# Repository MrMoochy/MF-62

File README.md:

All files are in master branch
Todos los archivos estan en la rama master

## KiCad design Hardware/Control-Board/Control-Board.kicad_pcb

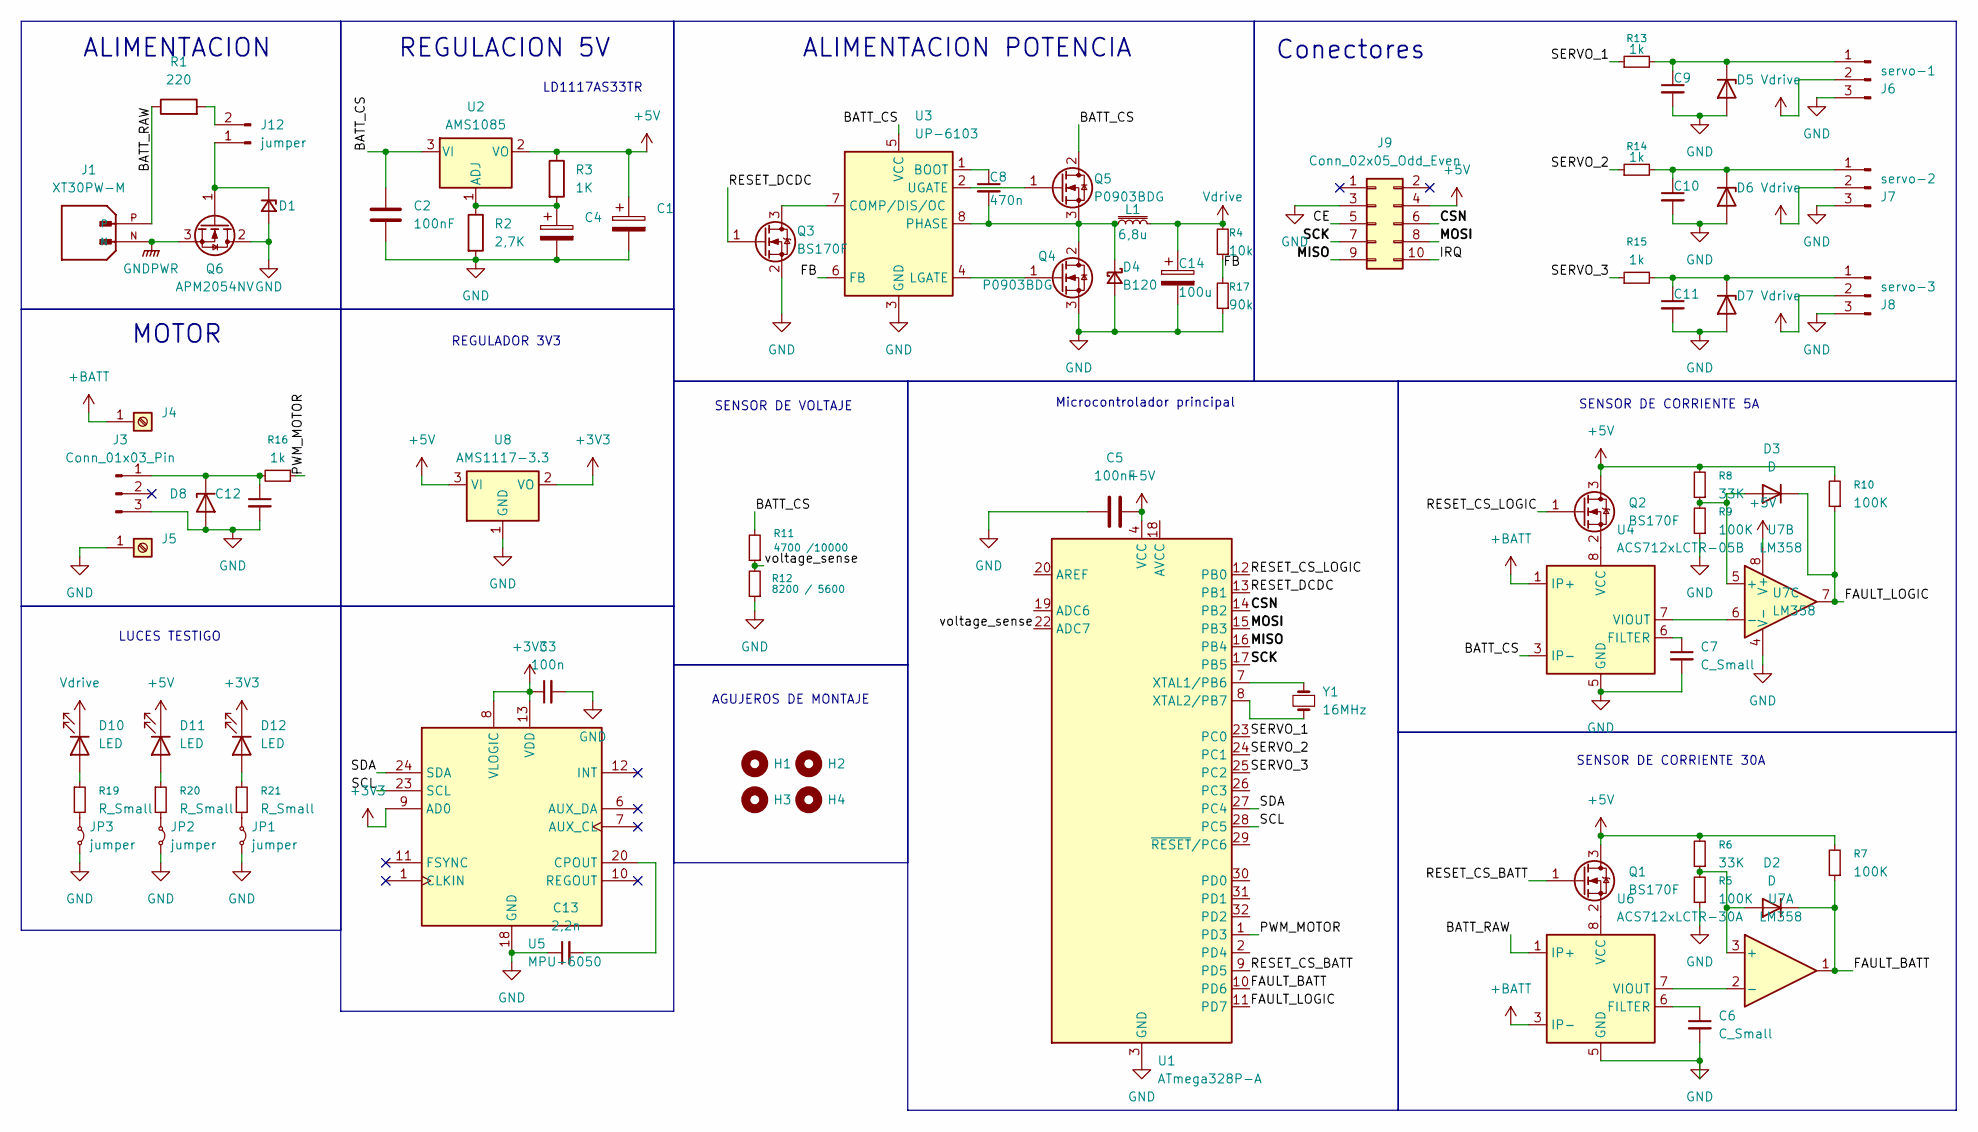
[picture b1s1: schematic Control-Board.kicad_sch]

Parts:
C1: 220uF / 10V; CP_Elec_6.3x4.5
C2: 100nF; C_0805_2012Metric_Pad1.18x1.45mm_HandSolder
C3: 100n; C_0805_2012Metric_Pad1.18x1.45mm_HandSolder
C4: <10uF / 10V; CP_Elec_5x4.4
C5: 100nF; C_0402_1005Metric_Pad0.74x0.62mm_HandSolder
C6, C7, C9, C10, C11, C12: C_Small; C_0805_2012Metric_Pad1.18x1.45mm_HandSolder
C8: 470n; C_0805_2012Metric_Pad1.18x1.45mm_HandSolder
C13: 2,2n; C_0805_2012Metric_Pad1.18x1.45mm_HandSolder
C14: 100u; CP_Elec_5x5.7
D1: mmsz5246bt1g; D_SOD-123
D2, D3: D; D_SOD-123
D4: B120; D_SMA
D5, D6, D7, D8: ESD5Zxx; D_SOD-523
D10, D11, D12: LED; LED_0805_2012Metric_Pad1.15x1.40mm_HandSolder
H1, H2, H3, H4: Mounting_Hole; MountingHole_2.2mm_M2_ISO7380
J1: XT30PW-M; AMASS_XT30PW-M; PARTREV 1.2
J3: Conn_01x03_Pin; PinHeader_1x03_P2.54mm_Horizontal
J4, J5: Screw_Terminal_01x01; Cable_Doble_1,5mm
J6: servo-1; PinHeader_1x03_P2.54mm_Horizontal
J7: servo-2; PinHeader_1x03_P2.54mm_Horizontal
J8: servo-3; PinHeader_1x03_P2.54mm_Horizontal
J9: Conn_02x05_Odd_Even; IDC-Header_2x05_P2.54mm_Horizontal
J12: jumper; PinHeader_1x02_P2.54mm_Vertical
JP1, JP2, JP3: jumper; R_0805_2012Metric_Pad1.20x1.40mm_HandSolder
L1: 6,8u; L_6.3x6.3_H3
Q1, Q2, Q3: BS170F; SOT-23
Q4, Q5: P0903BDG; TO-252-2
Q6: APM2054NV; TO-252-2
R1: 220; R_0805_2012Metric_Pad1.20x1.40mm_HandSolder
R2: 2,7K; R_0805_2012Metric_Pad1.20x1.40mm_HandSolder
R3: 1K; R_0805_2012Metric_Pad1.20x1.40mm_HandSolder
R4: 10k; R_0805_2012Metric_Pad1.20x1.40mm_HandSolder
R5, R7, R9, R10: 100K; R_0805_2012Metric_Pad1.20x1.40mm_HandSolder
R6, R8: 33K; R_0805_2012Metric_Pad1.20x1.40mm_HandSolder
R11: 4700 /10000; R_0805_2012Metric_Pad1.20x1.40mm_HandSolder
R12: 8200 / 5600; R_0805_2012Metric_Pad1.20x1.40mm_HandSolder
R13, R14, R15, R16: 1k; R_0805_2012Metric_Pad1.20x1.40mm_HandSolder
R17: 90k; R_0805_2012Metric_Pad1.20x1.40mm_HandSolder
R19, R20, R21: R_Small; R_0805_2012Metric_Pad1.20x1.40mm_HandSolder
U1: ATmega328P-A; TQFP-32_7x7mm_P0.8mm
U2: AMS1085; TO-252-2
U3: UP-6103; SOIC-8_3.9x4.9mm_P1.27mm
U4: ACS712xLCTR-05B; SOIC-8_3.9x4.9mm_P1.27mm
U5: MPU-6050; InvenSense_QFN-24_4x4mm_P0.5mm
U6: ACS712xLCTR-30A; SOIC-8_3.9x4.9mm_P1.27mm
U7: LM358; SOIC-8_3.9x4.9mm_P1.27mm
U8: AMS1117-3.3; SOT-223-3_TabPin2
Y1: 16MHz; Crystal_SMD_3215-2Pin_3.2x1.5mm

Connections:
+3V3: C3.1, D12.1 (K), U5.8 (VLOGIC), U5.9 (AD0), U5.13 (VDD), U8.2 (VO)
+5V: C1.1, C5.2, D11.1 (K), J9.4, Q1.3 (D), Q2.3 (D), R3.1, R6.2, R7.2, R8.2, R10.2, U1.4 (VCC), U1.6 (VCC), U2.2 (VO), U7.8 (V+), U8.3 (VI)
+BATT: J4.1, U4.1 (IP+), U4.2 (IP+), U6.3 (IP-), U6.4 (IP-)
/BATT_CS: C2.1, Q5.2 (D), R11.2, U2.3 (VI), U3.5 (VCC), U4.3 (IP-), U4.4 (IP-)
/BATT_RAW: J1.P, R1.1, U6.1 (IP+), U6.2 (IP+)
/CE: J9.5
/CSN: J9.6, U1.14 (PB2)
/FAULT_BATT: D2.1 (K), R7.1, U1.10 (PD6), U7.1
/FAULT_LOGIC: D3.1 (K), R10.1, U1.11 (PD7), U7.7
/FB: R4.1, R17.2, U3.6 (FB)
/IRQ: J9.10
/MISO: J9.9, U1.16 (PB4)
/MOSI: J9.8, U1.15 (PB3)
/PWM_MOTOR: R16.1, U1.1 (PD3)
/RESET_CS_BATT: Q1.1 (G), U1.9 (PD5)
/RESET_CS_LOGIC: Q2.1 (G), U1.12 (PB0)
/RESET_DCDC: Q3.1 (G), U1.13 (PB1)
/SCK: J9.7, U1.17 (PB5)
/SCL: U1.28 (PC5), U5.23 (SCL)
/SDA: U1.27 (PC4), U5.24 (SDA)
/SERVO_1: R13.1, U1.23 (PC0)
/SERVO_2: R14.1, U1.24 (PC1)
/SERVO_3: R15.1, U1.25 (PC2)
/voltage_sense: R11.1, R12.2, U1.22 (ADC7)
GND: C1.2, C2.2, C3.2, C4.2, C5.1, C6.2, C7.2, C9.2, C10.2, C11.2, C12.2, C13.1, C14.2, D1.2 (A), D4.2 (A), D5.2 (A), D6.2 (A), D7.2 (A), D8.2 (A), J3.3, J5.1, J6.3, J7.3, J8.3, J9.3, JP1.2 (B), JP2.2 (B), JP3.2 (B), Q3.2 (S), Q4.3 (S), Q6.2 (D), R2.2, R5.1, R9.1, R12.1, R17.1, U1.3 (GND), U1.5 (GND), U1.21 (GND), U3.3 (GND), U4.5 (GND), U5.18 (GND), U6.5 (GND), U7.4 (V-), U8.1 (GND)
GNDPWR: J1.N, Q6.3 (S)
unnamed: D1.1 (K), J12.1, Q6.1 (G)
unnamed: D2.2 (A), R5.2, R6.1, U7.3 (+)
unnamed: D3.2 (A), R8.1, R9.2, U7.5 (+)
unnamed: C8.2, D4.1 (K), L1.1, Q4.2 (D), Q5.3 (S), U3.8 (PHASE)
unnamed: C9.1, D5.1 (K), J6.1, R13.2
unnamed: C10.1, D6.1 (K), J7.1, R14.2
unnamed: C11.1, D7.1 (K), J8.1, R15.2
unnamed: C12.1, D8.1 (K), J3.1, R16.2
unnamed: D10.2 (A), R19.1
unnamed: D11.2 (A), R20.1
unnamed: D12.2 (A), R21.1
unnamed: J12.2, R1.2
unnamed: JP1.1 (A), R21.2
unnamed: JP2.1 (A), R20.2
unnamed: JP3.1 (A), R19.2
unnamed: Q1.2 (S), U6.8 (VCC)
unnamed: Q2.2 (S), U4.8 (VCC)
unnamed: Q3.3 (D), U3.7 (COMP/DIS/OC)
unnamed: Q4.1 (G), U3.4 (LGATE)
unnamed: Q5.1 (G), U3.2 (UGATE)
unnamed: U1.7 (XTAL1/PB6), Y1.2
unnamed: U1.8 (XTAL2/PB7), Y1.1
unnamed: C4.1, R2.1, R3.2, U2.1 (ADJ)
unnamed: C8.1, U3.1 (BOOT)
unnamed: C7.1, U4.6 (FILTER)
unnamed: U4.7 (VIOUT), U7.6 (-)
unnamed: C13.2, U5.20 (CPOUT)
unnamed: C6.1, U6.6 (FILTER)
unnamed: U6.7 (VIOUT), U7.2 (-)
Vdrive: C14.1, D10.1 (K), J6.2, J7.2, J8.2, L1.2, R4.2

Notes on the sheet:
ALIMENTACION
Microcontrolador principal
SENSOR DE VOLTAJE
REGULADOR 3V3
REGULACION 5V
ALIMENTACION POTENCIA
SENSOR DE CORRIENTE 5A
LD1117AS33TR
SENSOR DE CORRIENTE 30A
Conectores
LUCES TESTIGO
MOTOR
AGUJEROS DE MONTAJE

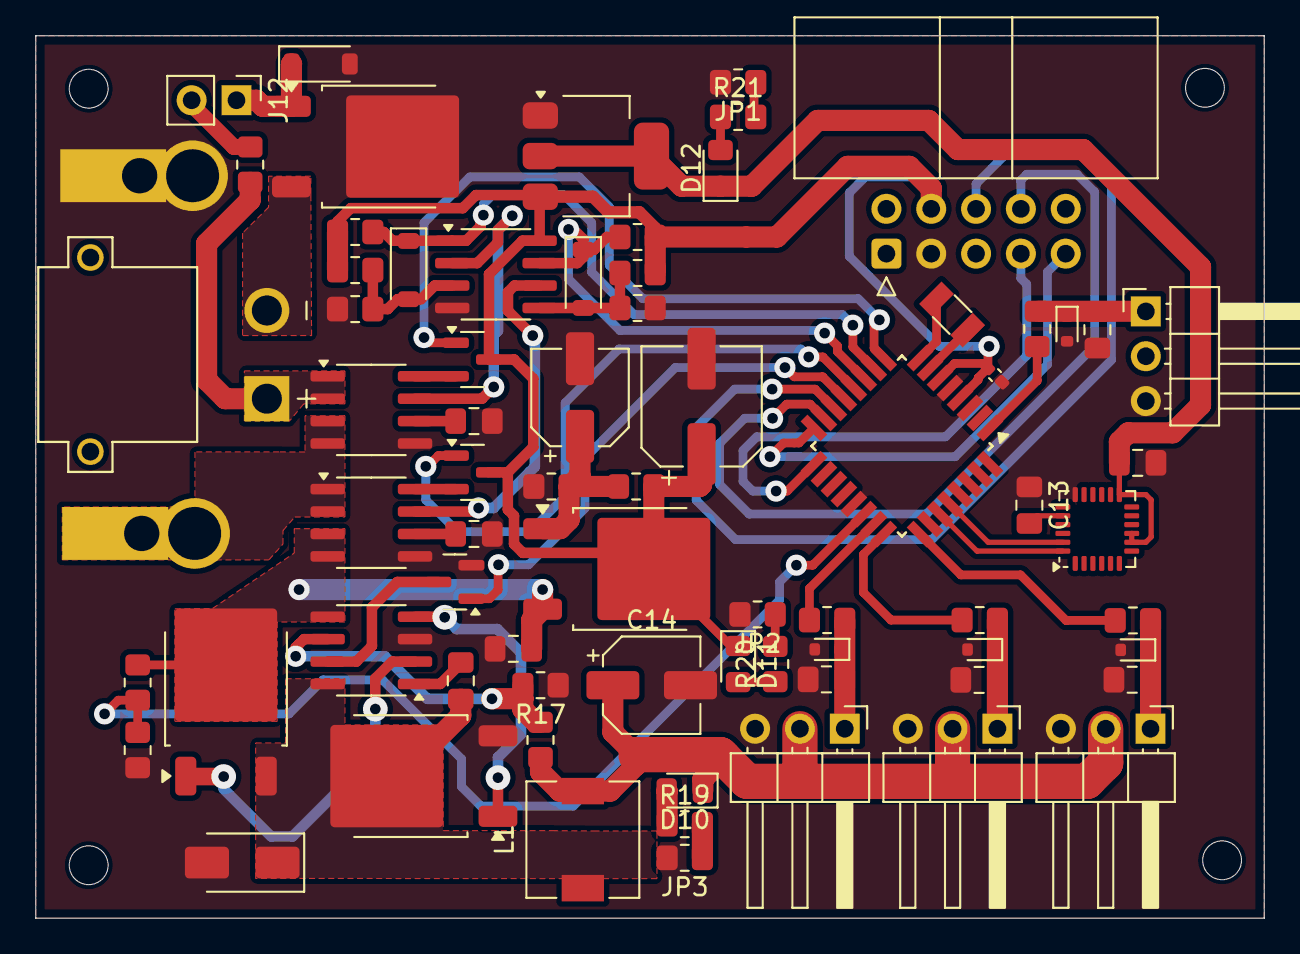
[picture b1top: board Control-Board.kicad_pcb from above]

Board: 2 copper layers, 69.6 x 50.0 mm, 77 parts (0 on the bottom side), 54 nets.

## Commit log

2025-12-09 Create Hardware
2025-12-09 Archivos del Avion
